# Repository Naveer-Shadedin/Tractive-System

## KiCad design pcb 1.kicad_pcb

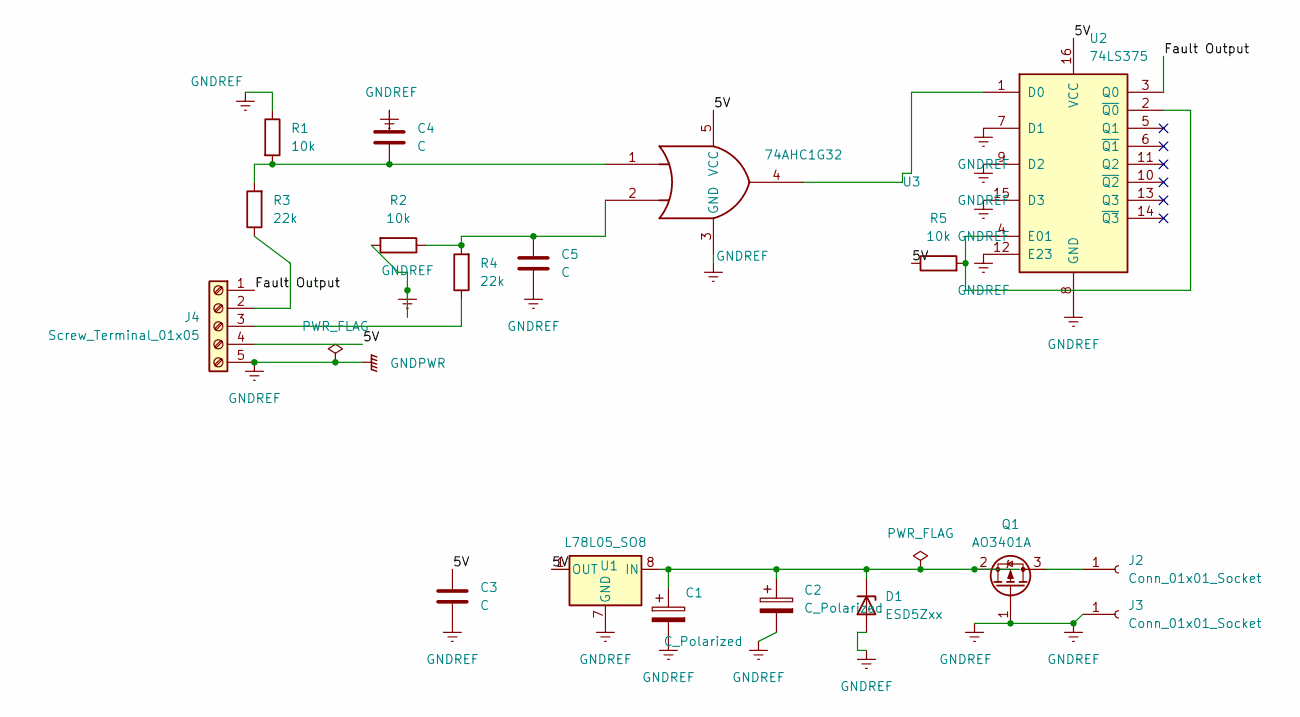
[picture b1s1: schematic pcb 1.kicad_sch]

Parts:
C1, C2: C_Polarized; CP_Elec_10x10.5
C3, C4, C5: C; C_Disc_D10.0mm_W2.5mm_P5.00mm
D1: ESD5Zxx; D_SOD-523
J2, J3: Conn_01x01_Socket; PinSocket_1x01_P2.00mm_Vertical
J4: Screw_Terminal_01x05; TerminalBlock_MaiXu_MX126-5.0-05P_1x05_P5.00mm
Q1: AO3401A; SOT-23
R1, R2, R5: 10k; R_01005_0402Metric_Pad0.57x0.30mm_HandSolder
R3, R4: 22k; R_01005_0402Metric_Pad0.57x0.30mm_HandSolder
U1: L78L05_SO8; SOIC-8_3.9x4.9mm_P1.27mm
U2: 74LS375; N16
U3: 74AHC1G32; SOT25_DIO

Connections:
/5V: C3.1, J4.4, R5.1, U1.1 (OUT), U2.16 (VCC), U3.5 (VCC)
/Fault Output: J4.1, U2.3 (Q0)
GNDPWR: C1.2, C2.2, C3.2, C4.1, C5.2, D1.2 (A), J3.1 (Pin_1_1), J4.5, Q1.1 (G), R1.1, R2.2, U1.2 (GND), U1.3 (GND), U1.6 (GND), U1.7 (GND), U2.7 (D1), U2.8 (GND), U2.9 (D2), U2.12 (E23), U2.15 (D3), U3.3 (GND)
unnamed: C4.2, R1.2, R3.2, U3.1
unnamed: C5.1, R2.1, R4.2, U3.2
unnamed: C1.1, C2.1, D1.1 (K), Q1.2 (S), U1.8 (IN)
unnamed: J2.1 (Pin_1_1), Q1.3 (D)
unnamed: J4.2, R3.1
unnamed: J4.3, R4.1
unnamed: U2.1 (D0), U3.4
unnamed: R5.2, U2.2 (~Q0), U2.4 (E01)

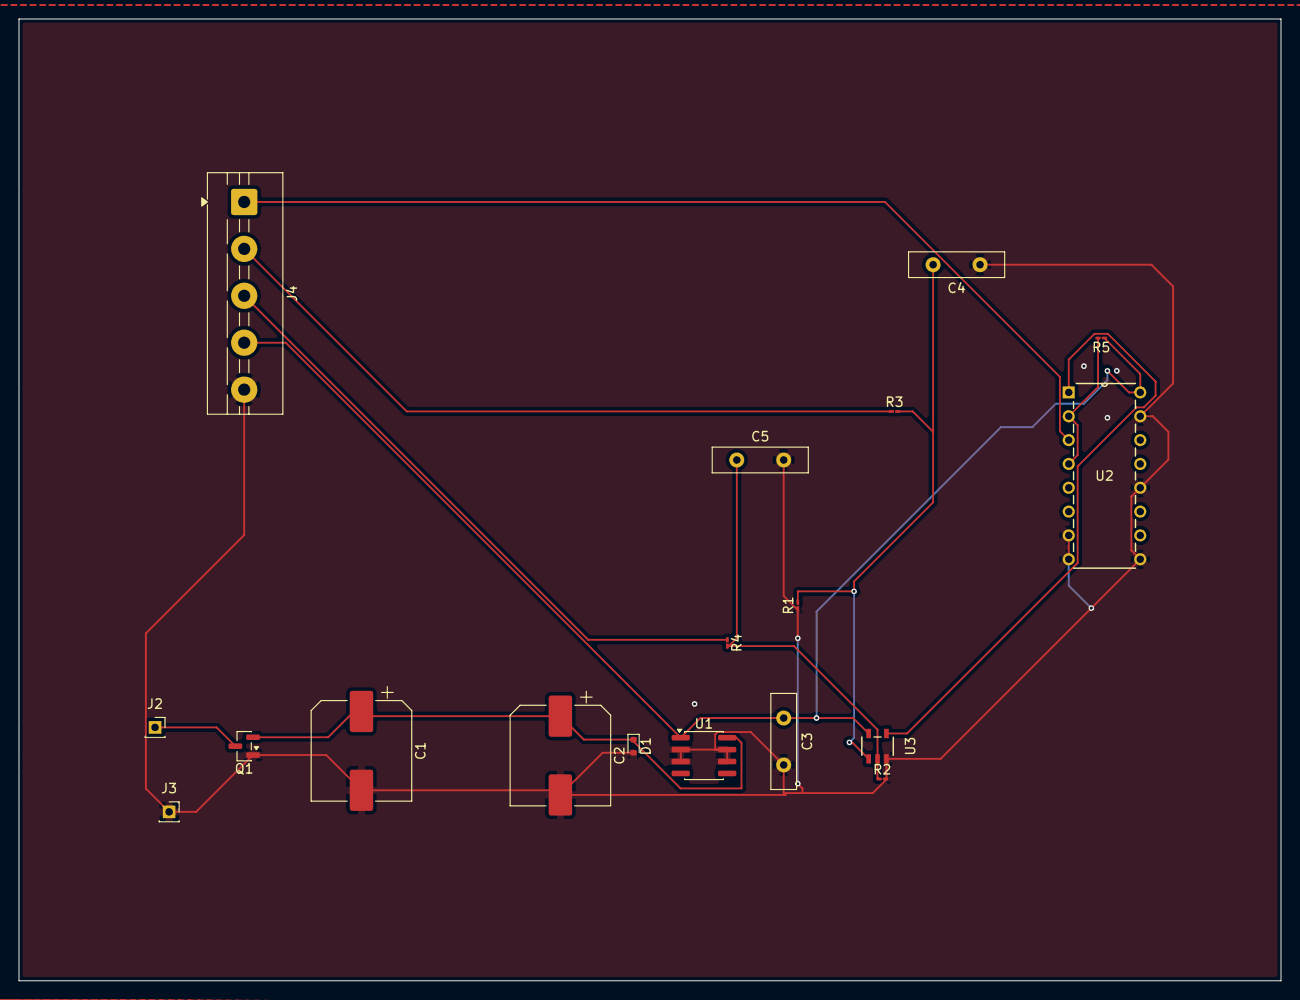
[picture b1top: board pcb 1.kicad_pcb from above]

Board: 2 copper layers, 134.5 x 102.5 mm, 18 parts (0 on the bottom side), 11 nets.
